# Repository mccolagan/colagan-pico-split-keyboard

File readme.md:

# ⌨️ Colagan V2 Right Only

> Clavier split custom - moitié droite uniquement avec layout AZERTY français

📖 **Page du projet :** https://mccolagan.github.io/colagan-pico-split-keyboard/ · 🛠️ Matériel (KiCad, PCB V2) : [`hardware/`](hardware/README.md)

> **Firmware actuel : split Vial des deux moitiés**, documenté dans [`firmware/README.md`](firmware/README.md)
> (compilation, flash, couches, couleurs par couche éditables depuis le configurateur web, protocole
> [`docs/led-stream-protocol.md`](docs/led-stream-protocol.md)). La suite de ce fichier décrit l'ancien
> firmware VIA « Right Only » et est conservée pour référence.

---

## ✨ Caractéristiques

- 🧠 **Processeur:** RP2040 (Raspberry Pi Pico)
- ⌨️ **Layout:** 30 touches (matrice 6×5)
- 🔌 **Configuration:** VIA (reconfiguration en temps réel)
- 💡 **RGB:** 30 LEDs SK6812 MINI-E (1 par touche) avec animations personnalisées
- 🖐️ **Ergonomie:** Ligne 5 en forme de "montagne" pour les pouces
- 🇫🇷 **Optimisé:** AZERTY français

---

## 🎮 Layers disponibles

Le clavier dispose de **6 layers**. Il est pensé pour jouer de la main droite (souris à gauche) : les couches de jeu envoient les **touches par défaut du jeu**, placées sous les doigts, pour ne jamais avoir à rebinder.

| Layer | Rôle | Accès |
|-------|------|-------|
| **BASE** | Côté droit de l'AZERTY | Défaut |
| **FN** | Côté gauche de l'AZERTY | Double-tap sur Ctrl |
| **FPS** | Warzone | Sélecteur |
| **MMO** | WoW | Sélecteur |
| **MMO_UI** | F1-F5 et fenêtres du jeu | Tenir la touche `UI` depuis MMO |
| **SEL** | Sélecteur de couche | Triple-tap sur Ctrl, ou tenir le pouce de droite en jeu |

### 🔀 Changer de layer

La touche de pouce tout à droite (matrice 4,4) fait office de Ctrl multi-tap sur BASE et FN (fenêtre de 500 ms entre deux taps) :

| Taps | Effet |
|------|-------|
| **1x** | Ctrl normal |
| **2x** | Toggle FN |
| **3x** | Ouvre/ferme le sélecteur SEL |

Dans le sélecteur, la rangée du haut propose : **BASE** (blanc), **FPS** (rouge), **MMO** (bleu), **FN** (vert). Un appui choisit la couche. Depuis FPS ou MMO, on **tient** le pouce de droite (en vert), on appuie sur la couche voulue, puis on relâche.

### 🎯 Layer BASE - Côté DROIT AZERTY

```
┌─────┬─────┬─────┬─────┬─────┬─────┐
│  -  │  è  │  _  │  ç  │  à  │  )  │
├─────┼─────┼─────┼─────┼─────┼─────┤
│  Y  │  U  │  I  │  O  │  P  │  ^  │
├─────┼─────┼─────┼─────┼─────┼─────┤
│  H  │  J  │  K  │  L  │  M  │  ù  │
├─────┼─────┼─────┼─────┼─────┼─────┤
│  B  │  N  │  ,  │  ;  │  :  │  !  │
├─────┼─────┼─────┼─────┼─────┼─────┤
│ Del │Bksp │ Ent │ Alt │Ctrl │     │
│     │     │     │     │ 2xFN│     │
└─────┴─────┴─────┴─────┴─────┴─────┘
```

### 🔤 Layer FN - Côté GAUCHE AZERTY

Double-tap sur Ctrl pour activer/désactiver

```
┌─────┬─────┬─────┬─────┬─────┬─────┐
│  ²  │  &  │  é  │  "  │  '  │  (  │
├─────┼─────┼─────┼─────┼─────┼─────┤
│ Tab │  A  │  Z  │  E  │  R  │  T  │
├─────┼─────┼─────┼─────┼─────┼─────┤
│Caps │  Q  │  S  │  D  │  F  │  G  │
├─────┼─────┼─────┼─────┼─────┼─────┤
│Shift│  <  │  W  │  X  │  C  │  V  │
├─────┼─────┼─────┼─────┼─────┼─────┤
│ Del │Bksp │ Ent │ Alt │Ctrl │     │
└─────┴─────┴─────┴─────┴─────┴─────┘
```

### 🔫 Layer FPS - Warzone

Touches par défaut du jeu (AZERTY côté OS). Le cluster ZQSD est au même endroit que sur la couche MMO.

```
┌─────┬─────┬─────┬─────┬─────┬─────┐
│  1  │  2  │  3  │  4  │  5  │ Tab │
├─────┼─────┼─────┼─────┼─────┼─────┤
│  C  │Shift│  Z  │  E  │  F  │  G  │
├─────┼─────┼─────┼─────┼─────┼─────┤
│  X  │  Q  │  S  │  D  │  R  │  V  │
├─────┼─────┼─────┼─────┼─────┼─────┤
│  M  │  T  │  /  │Bksp │ Ent │ Esc │
├─────┼─────┼─────┼─────┼─────┼─────┘
│ Spc │Ctrl │ Alt │     │ SEL │
└─────┴─────┴─────┴─────┴─────┘
```

### ⚔️ Layer MMO - WoW

`S1` à `S11` sont des emplacements de sorts, à lier dans le jeu (ou à remapper dans VIA). Shift, Ctrl et Alt aux pouces multiplient chaque emplacement.

```
┌─────┬─────┬─────┬─────┬─────┬─────┐
│ S1  │ S2  │ S3  │ S4  │ S5  │ S6  │
├─────┼─────┼─────┼─────┼─────┼─────┤
│ Tab │  A  │  Z  │  E  │ S7  │ S8  │
├─────┼─────┼─────┼─────┼─────┼─────┤
│NumLk│  Q  │  S  │  D  │ S9  │ S10 │
├─────┼─────┼─────┼─────┼─────┼─────┤
│ S11 │ UI  │  /  │Bksp │ Ent │ Esc │
├─────┼─────┼─────┼─────┼─────┼─────┘
│ Spc │Shift│Ctrl │ Alt │ SEL │
└─────┴─────┴─────┴─────┴─────┘
```

`S1` à `S10` envoient `1` à `0` (AZERTY : `& é " ' ( - è _ ç à`), `S11` envoie `-`. Tenir `UI` ouvre la sous-couche **MMO_UI** :

```
┌─────┬─────┬─────┬─────┬─────┬─────┐
│ F1  │ F2  │ F3  │ F4  │ F5  │  P  │
├─────┼─────┼─────┼─────┼─────┼─────┤
│     │     │     │     │  C  │  B  │
├─────┼─────┼─────┼─────┼─────┼─────┤
│     │     │     │     │  M  │  N  │
├─────┼─────┼─────┼─────┼─────┼─────┤
│  L  │     │     │     │     │     │
└─────┴─────┴─────┴─────┴─────┴─────┘
```

Les cases vides gardent la touche de la couche MMO.

### 🎛️ Layer SEL - Sélecteur

```
┌─────┬─────┬─────┬─────┬─────┬─────┐
│BASE │ FPS │ MMO │ FN  │     │     │
├─────┼─────┼─────┼─────┼─────┼─────┤
│ Br- │ Br+ │     │     │     │     │
└─────┴─────┴─────┴─────┴─────┴─────┘
```

**Couleurs RGB des couches de jeu :**
- 🔵 **BLEU** : armes 1-5 (FPS), sorts (MMO)
- ⚪ **BLANC** : ZQSD + Espace
- 🟡 **JAUNE** : modificateurs, Tab
- 🔴 **ROUGE** : actions de jeu (FPS)
- 🟣 **VIOLET** : touches de menu (Échap, Entrée, Retour, `/`)
- 🟢 **VERT** : sélecteur de couche, `UI`
- ⚫ **ÉTEINT** : touches inutilisées

La luminosité se règle depuis le sélecteur (**Br-** / **Br+**).

---

## 🚀 Quick Start

### 1️⃣ Compiler le firmware

```bash
./build.sh
```

Ce script :
- Synchronise les fichiers du projet vers QMK
- Compile le firmware
- Copie le `.uf2` dans le projet

### 2️⃣ Flasher le Pico

**Entrer en mode bootloader :**

- 🔹 **Méthode 1 :** Maintenir `BOOT` + appuyer `RESET` + relâcher `BOOT`
- 🔹 **Méthode 2 :** Double-tap rapide sur `RESET`

**Flasher automatiquement :**

```bash
./flash.sh
```

**Ou manuellement :**

```bash
sudo cp firmware.uf2 /media/$USER/RPI-RP2*/
```

✅ Le clavier redémarre automatiquement !

### 3️⃣ Reset EEPROM (première utilisation)

Pour appliquer la configuration par défaut du firmware (luminosité 10%, etc.) :

**Bootmagic Reset :**
1. Débranchez le clavier
2. Maintenez la touche en haut à gauche (position 0,0 - la touche "-")
3. Rebranchez le clavier tout en maintenant la touche
4. L'EEPROM sera réinitialisée

---

## 📁 Structure des fichiers

```
colagan-pico-split-keyboard/
├── 🔨 build.sh                    # Script de compilation + synchronisation
├── ⚡ flash.sh                    # Script de flash automatique
├── 📦 firmware.uf2                # Firmware compilé
├── ⚙️ keyboard.json               # Configuration matérielle QMK
├── 📖 readme.md                   # Ce fichier
└── 🗂️ keymaps/
    └── via/                       # Keymap VIA
        ├── keymap.c               # Layout des touches + RGB custom
        └── config.h               # Configuration (6 layers, luminosité)
```

---

## 🔧 Configuration matérielle

### 📌 Pins GPIO

- **Colonnes (6) :** `GP20`, `GP22`, `GP12`, `GP11`, `GP10`, `GP9`
- **Lignes (5) :** `GP21`, `GP19`, `GP18`, `GP17`, `GP16`
- **RGB LEDs :** `GP13` (SK6812 MINI-E data)

### 💡 RGB Matrix

- **LEDs :** 30 SK6812 MINI-E (1 par touche)
- **Câblage :** Serpentin (ligne 0: L→R, ligne 1: R→L, etc.)
- **Luminosité par défaut :** 10% (26/255)
- **Luminosité max :** 200/255

### 🔌 USB VID/PID

- **Vendor ID :** `0xFEED`
- **Product ID :** `0x0004`
- **Nom :** Colagan V2 Right Only

---

## 🎨 RGB Matrix

### Modes RGB

> Firmware Vial split : couleurs et effet par couche se règlent dans le configurateur web, voir
> [`firmware/README.md`](firmware/README.md#modifier-les-led). Ce qui suit concerne l'ancien firmware.

Le clavier dispose de 2 modes RGB distincts :

1. **Layers BASE/FN** : Animations RGB Matrix standards (40+ effets)
2. **Layers FPS/MMO/SEL** : Couleurs fixes personnalisées par touche (voir schémas ci-dessus)

### Contrôles RGB via VIA

Dans VIA (onglet **Lighting** → **QMK RGB Matrix**) :

| Keycode   | Action                         |
|-----------|--------------------------------|
| `RM_TOGG` | 💡 On/Off des LEDs            |
| `RM_NEXT` | ➡️ Animation suivante         |
| `RM_PREV` | ⬅️ Animation précédente       |
| `RM_VALU` | ☀️ Augmenter la luminosité    |
| `RM_VALD` | 🌙 Diminuer la luminosité     |
| `RM_HUEU` | 🔴 Augmenter la teinte        |
| `RM_HUED` | 🔵 Diminuer la teinte         |
| `RM_SATU` | ⬆️ Augmenter la saturation    |
| `RM_SATD` | ⬇️ Diminuer la saturation     |
| `RM_SPDU` | ⚡ Vitesse d'animation +       |
| `RM_SPDD` | 🐌 Vitesse d'animation -       |

**Note :** Sur les layers FPS, MMO et SEL, seuls les contrôles de luminosité (Br-/Br+ du sélecteur) fonctionnent. Les autres effets sont désactivés pour maintenir les couleurs personnalisées.

---

## 🎹 Configuration VIA

### 🔄 Correspondances AZERTY ↔ QWERTY

> ⚠️ VIA affiche en **QWERTY US**, mais votre OS utilise **AZERTY français**

| 🇫🇷 Pour obtenir (AZERTY) | 🇺🇸 Sélectionner dans VIA |
|---------------------------|---------------------------|
| `'` (apostrophe)          | `4`                       |
| `é`                       | `2`                       |
| `è`                       | `7`                       |
| `à`                       | `0`                       |
| `ù`                       | `'` (quote)               |
| `ç`                       | `9`                       |
| `-` (tiret)               | `6`                       |
| `A`                       | `Q`                       |
| `Q`                       | `A`                       |
| `W`                       | `Z`                       |
| `Z`                       | `W`                       |
| `M`                       | `;`                       |
| `,` (virgule)             | `M`                       |

---

## 🛠️ Dépannage

### ❌ VIA ne détecte pas le clavier

1. ✅ Vérifiez que le firmware a été compilé avec `-km via`
2. 🔄 Rechargez la page VIA
3. 🔌 Vérifiez la connexion USB :
   ```bash
   lsusb | grep -i feed
   # Devrait afficher : ID feed:0004 Colagan V2 Right Only
   ```

### 🔤 Les touches ne correspondent pas

➡️ **Normal !** VIA affiche en QWERTY, votre OS est en AZERTY.
📋 Référez-vous au tableau de correspondances ci-dessus.

### 💡 Le clavier démarre avec des couleurs RGB étranges

C'est normal ! Le clavier démarre en layer BASE avec les animations RGB par défaut.

Pour utiliser les layers de jeu :
- Triple-tap sur Ctrl (touche en bas à droite), puis choisir FPS ou MMO

Pour désactiver le RGB au démarrage :
- Utilisez VIA pour assigner `RM_TOGG` à une touche et éteindre le RGB

### 🎮 Les layers de jeu ne démarrent pas avec la bonne luminosité

Si la luminosité est à 0 après un flash :

1. Débranchez le clavier
2. Maintenez la touche en haut à gauche ("-")
3. Rebranchez le clavier (Bootmagic Reset)
4. La luminosité sera réinitialisée à 10%

### 🔄 Reset de la configuration

**Bootmagic Reset (recommandé) :**
- Débranchez le clavier
- Maintenez la touche en haut à gauche (L0C0)
- Rebranchez le clavier

**Via VIA :**
- Settings ⚙️ → "Clear EEPROM"
- Déconnectez/reconnectez le clavier

---

## 📚 Commandes utiles

```bash
# 🔨 Compiler et synchroniser
./build.sh

# ⚡ Flasher
./flash.sh

# 🧹 Nettoyer les fichiers de compilation
cd ~/qmk_firmware
~/qmk_env/bin/qmk clean

# 🩺 Vérifier la configuration QMK
~/qmk_env/bin/qmk doctor

# ℹ️ Informations du clavier
~/qmk_env/bin/qmk info -kb colagan_v2_right_only
```

---

## 🔗 Ressources

- 🌐 [VIA Web App](https://usevia.app)
- 📖 [Documentation VIA](https://www.caniusevia.com/)
- 📚 [Documentation QMK](https://docs.qmk.fm/)
- 🔧 [QMK VIA Support](https://docs.qmk.fm/features/via)
- 🔌 [Configuration RP2040](https://docs.qmk.fm/platformdev_rp2040)

---

## 📄 License

GPL-2.0-or-later

---

## 🎯 Notes de développement

### Custom RGB Gaming Layers

Les layers FPS, MMO et SEL utilisent `rgb_matrix_indicators_user()` pour définir des couleurs personnalisées par touche :
- Les couleurs sont proportionnelles à la luminosité globale (`rgb_matrix_get_val()`)
- Les touches Br+/Br- (layer SEL) appellent directement `rgb_matrix_increase_val()` et `rgb_matrix_decrease_val()`
- Le mapping LED suit la chaîne linéaire du PCB : index = ligne × 6 + colonne (pouces : 24 à 28)

### Multi-tap Ctrl Key

La touche Ctrl (position 4,4) utilise un système de multi-tap :
- Délai de détection : `CTRL_MULTITAP_TERM` (500ms)
- 1 tap : Ctrl normal
- 2 taps : Toggle layer FN
- 3 taps : Ouvre/ferme le sélecteur SEL (`TO()` vers BASE, FPS, MMO ou FN)

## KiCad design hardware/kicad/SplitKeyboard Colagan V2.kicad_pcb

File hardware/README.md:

# Matériel — Colagan Pico Split KeyBoard V2

Sources KiCad (9.0) du PCB réversible tel que fabriqué chez JLCPCB (novembre 2025) : 29 touches Gateron KS-33 low profile en hot-swap, une LED SK6812 mini-e et une diode par touche, Raspberry Pi Pico (W), USB-C 16 broches. Le même circuit sert pour les deux moitiés, en le retournant.

## Ouvrir le projet

Ouvrir `kicad/SplitKeyboard Colagan V2.kicad_pro` avec KiCad 9. Le fichier `fp-lib-table` déclare la bibliothèque d'empreintes du projet (`Library SplitKeyboard Colagan`), donc rien à configurer. Les symboles sont embarqués dans le schéma ; les bibliothèques standard de KiCad (`Connector`, `MCU_Module_RaspberryPi_Pico`, `power`, `MountingHole`) viennent de l'installation.

| Fichier | Contenu |
|---|---|
| `kicad/SplitKeyboard Colagan V2.kicad_{pro,sch,pcb}` | Projet principal (version fabriquée, 04/11/2025) |
| `kicad/Library SplitKeyboard Colagan.pretty/` | Toutes les empreintes personnalisées (voir ci-dessous) |
| `kicad/fp-lib-table` | Table de bibliothèques du projet |
| `kicad/fabrication-toolkit-options.json` | Options du plugin de fabrication |
| `images/` | Rendus 3D (face, dos), cuivre avant/arrière et schéma en SVG, générés avec `kicad-cli` |
| `3d/` | Export STEP et 3MF de la V1 (ancienne révision) |

Les anciennes sources (révision du 20/10/2025, variante OLED, captures) ne sont plus dans le dépôt : elles sont dans l'historique git.

## Empreintes (`Library SplitKeyboard Colagan.pretty`)

### Utilisées dans le PCB

| Empreinte | Rôle | Quantité |
|---|---|---|
| `KS33-HS-Colagan-1U-Final` | Touche 1U : interrupteur KS33 hot-swap, LED SK6812 mini-e, diode ; réversible (deux faces) | 25 |
| `KS33-HS-Colagan-1.5U-Final` | Même chose pour la colonne extérieure 1,5U | 4 |
| `RaspberryPi_Pico_Colagan_REF3` | Support du Raspberry Pi Pico | 1 |
| `USB_C_16P-Reversible-colagan` | Connecteur USB-C 16 broches (alimentation et lien série entre les moitiés) | 1 |
| `Capasitor_SMD_1206_Reversible_ColaganV3` | Résistances 5,1 kΩ de CC1/CC2 (R1, R2), réversibles | 2 |
| `qrcode github` | QR code du projet, en sérigraphie/cuivre | 1 |

La touche KS33 intègre trois composants en un seul placement : c'est une empreinte combinée, pas une empreinte d'interrupteur seule. Broches : 1 colonne, 2 et 3 ligne (via la diode), 4 +5V, 5 DIN de la LED, 6 GND, 7 DOUT de la LED.

### Versions intermédiaires et illustrations

- `Capasitor_*` autres que V3, `SOT-23-5-Reversible-*`, `USB_C_6P_Colagan`, `OLED_SSD1306_128x32_4pin`, `RaspberryPi_Pico_Colagan`, `_REF`, `_REF2` : itérations précédentes, non utilisées dans la V2.
- `Gengar*`, `Gengar_Souls.kicad_sym`, `fantominus*`, `spectrum 35mm` : illustrations de sérigraphie / cuivre (empreintes « LOGO »).

## Modèles 3D

Les empreintes référencent des modèles 3D qui **ne sont pas dans ce dépôt** :

- le modèle Gateron KS-33 low profile (`GateronKS-33LowProfile-3D/*.stp`, fourni par le fabricant) ;
- le modèle du switch de la bibliothèque `marbastlib` d'ebastler (installée via le gestionnaire de plugins de KiCad) ;
- un modèle `SK6812-E.step` stocké localement ;
- les modèles du Pico de la bibliothèque standard de KiCad.

Les empreintes fonctionnent sans eux ; seul l'affichage 3D dans KiCad en dépend. Le dossier `3d/` contient un export complet de la carte.

## Électronique

- **Matrice** : colonnes `Col0`–`Col5`, rangées `Row0`–`Row4`, diodes sur les touches. Brochage du Pico : colonnes GP20, GP22, GP12, GP11, GP10, GP9 ; rangées GP21, GP19, GP18, GP17, GP16 ; LEDs GP13.
- **LEDs** : chaîne linéaire, LED n = touche CH(n+1) (CH1 à CH29, de gauche à droite sur chaque rangée). Alimentées en 5 V.
- **Signal LED** : la ligne de données du Pico (3,3 V) attaque directement la première LED, sans convertisseur de niveau ni résistance (validé sur les deux moitiés, LED alimentées en 5 V). Les sources V2 n'ont pas de U3 ni de 4k7.
- **USB-C** : prise `J2` 16 broches (V2), avec deux résistances de 5,1 kΩ (R1, R2) sur CC1/CC2. Les broches de données D+/D- (A6/B6, A7/B7) sont reliées directement aux signaux `SCL` et `SDA` : c'est le lien série entre les deux moitiés.
- **Géométrie** : grille 6×4 au pas de 19,05 mm ; colonne extérieure 1,5U ; cinq pouces CH25–CH29 en arc (rotations 45°, 22,5°, 0°, −22,5°, −45° dans KiCad).

Brochage de la moitié gauche (carte retournée) : voir la section de montage ci-dessous. Détails lus sur le PCB V2 et validés sur les deux moitiés en octobre 2026.

## Non inclus

Les exports STEP lourds, les modèles 3D du switch, les Gerbers de fabrication et les sauvegardes automatiques de KiCad.

## Licence

Aucune licence matérielle n'est encore déclarée pour ces fichiers.

## Montage de la moitié gauche (retournée)

Le PCB est réversible : la gauche est la même carte retournée, avec le Pico dans le même sens. Conséquences vérifiées en octobre 2026 :
- Les étiquettes `NO PIN` et `+5V` sont inversées côté gauche. Les deux trous sont sur le rail 5 V : souder VBUS (broche 40 du Pico) dans l'un, ne jamais souder GP0 (broche 1) dans l'autre, sous peine d'injecter 5 V dans un GPIO.
- Le brochage est le miroir de la droite : LED sur GP18 (GP13 à droite), matrice colonnes GP11, GP9, GP19, GP20, GP21, GP22 et lignes GP10, GP12, GP13, GP14, GP15, lien série sur GP26.
- SK6812 mini-E : la broche marquée de la LED est le GND, pas le VDD. Souder à la pâte a donné des contacts intermittents, mieux vaut un fer.
- Diodes : cathode côté ligne (`COL2ROW`), le sens visuel est inversé d'une face à l'autre.

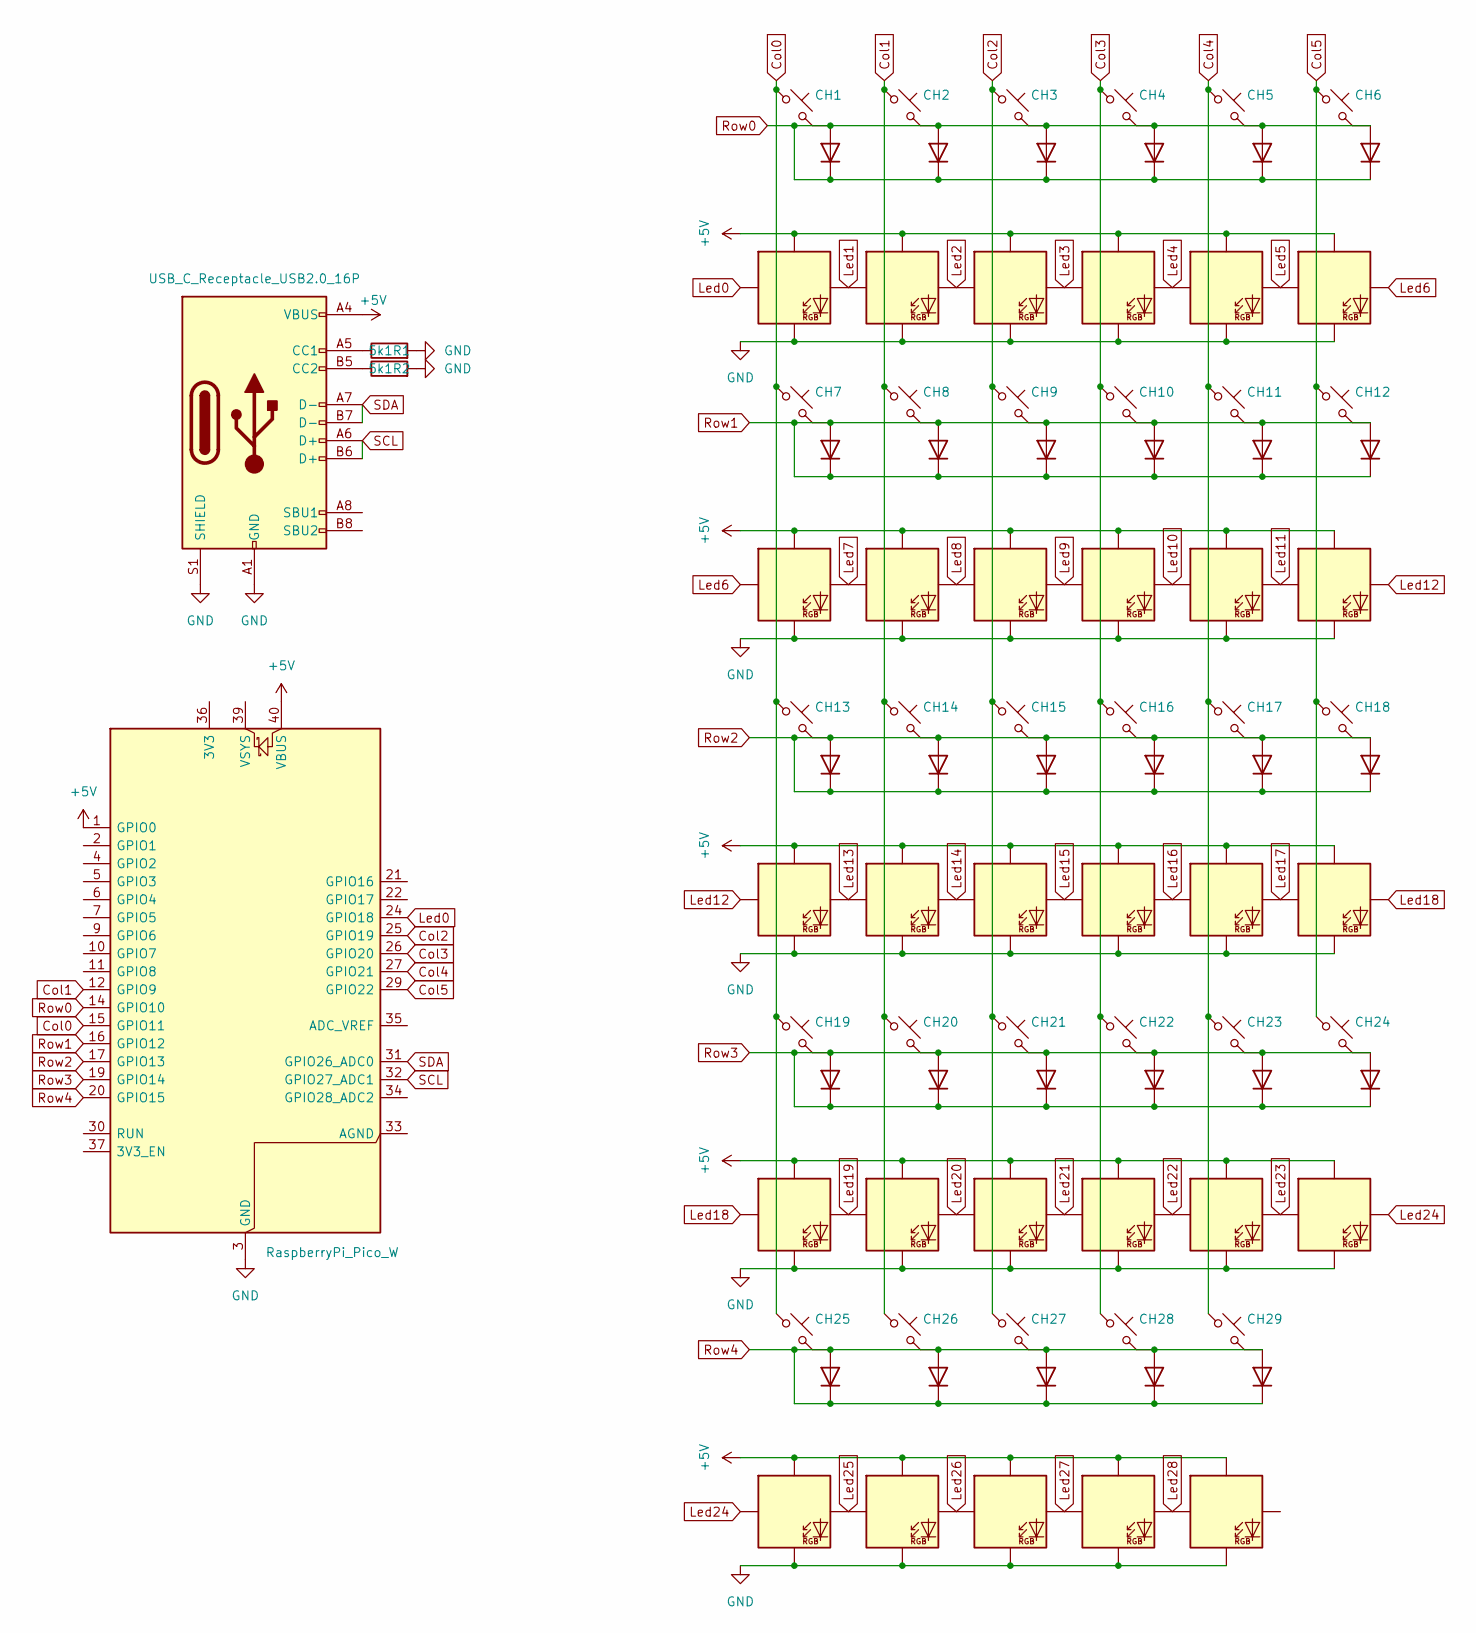
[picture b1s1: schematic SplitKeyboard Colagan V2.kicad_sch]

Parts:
5k1R1: R1; Capasitor_SMD_1206_Reversible_ColaganV3
5k1R2: Capasitor_SMD_1206_Reversible_ColaganV3
A1: RaspberryPi_Pico_W; RaspberryPi_Pico_Colagan_REF3
CH1, CH2, CH3, CH4, CH5, CH7, CH8, CH9, CH10, CH11, CH13, CH14, CH15, CH16, CH17, CH19, CH20, CH21, CH22, CH23, CH25, CH26, CH27, CH28, CH29: KS33_SW_HS; KS33-HS-Colagan-1U-Final
CH6, CH12, CH18, CH24: KS33_SW_HS; KS33-HS-Colagan-1.5U-Final
J2: USB_C_Receptacle_USB2.0_16P; USB_C_16P-Reversible-colagan

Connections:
+5V: A1.1 (GPIO0), A1.40 (VBUS), CH1.4 (VDD), CH2.4 (VDD), CH3.4 (VDD), CH4.4 (VDD), CH5.4 (VDD), CH6.4 (VDD), CH7.4 (VDD), CH8.4 (VDD), CH9.4 (VDD), CH10.4 (VDD), CH11.4 (VDD), CH12.4 (VDD), CH13.4 (VDD), CH14.4 (VDD), CH15.4 (VDD), CH16.4 (VDD), CH17.4 (VDD), CH18.4 (VDD), CH19.4 (VDD), CH20.4 (VDD), CH21.4 (VDD), CH22.4 (VDD), CH23.4 (VDD), CH24.4 (VDD), CH25.4 (VDD), CH26.4 (VDD), CH27.4 (VDD), CH28.4 (VDD), CH29.4 (VDD), J2.A4 (VBUS), J2.A9 (VBUS), J2.B4 (VBUS), J2.B9 (VBUS)
Col0: A1.15 (GPIO11), CH1.1, CH7.1, CH13.1, CH19.1, CH25.1
Col1: A1.12 (GPIO9), CH2.1, CH8.1, CH14.1, CH20.1, CH26.1
Col2: A1.25 (GPIO19), CH3.1, CH9.1, CH15.1, CH21.1, CH27.1
Col3: A1.26 (GPIO20), CH4.1, CH10.1, CH16.1, CH22.1, CH28.1
Col4: A1.27 (GPIO21), CH5.1, CH11.1, CH17.1, CH23.1, CH29.1
Col5: A1.29 (GPIO22), CH6.1, CH12.1, CH18.1, CH24.1
GND: 5k1R1.2, 5k1R2.2, A1.3 (GND), A1.8 (GND), A1.13 (GND), A1.18 (GND), A1.23 (GND), A1.28 (GND), A1.38 (GND), CH1.6 (VSS), CH2.6 (VSS), CH3.6 (VSS), CH4.6 (VSS), CH5.6 (VSS), CH6.6 (VSS), CH7.6 (VSS), CH8.6 (VSS), CH9.6 (VSS), CH10.6 (VSS), CH11.6 (VSS), CH12.6 (VSS), CH13.6 (VSS), CH14.6 (VSS), CH15.6 (VSS), CH16.6 (VSS), CH17.6 (VSS), CH18.6 (VSS), CH19.6 (VSS), CH20.6 (VSS), CH21.6 (VSS), CH22.6 (VSS), CH23.6 (VSS), CH24.6 (VSS), CH25.6 (VSS), CH26.6 (VSS), CH27.6 (VSS), CH28.6 (VSS), CH29.6 (VSS), J2.A1 (GND), J2.A12 (GND), J2.B1 (GND), J2.B12 (GND), J2.S1 (SHIELD)
Led0: A1.24 (GPIO18), CH1.5 (DIN)
Led1: CH1.7 (DOUT), CH2.5 (DIN)
Led2: CH2.7 (DOUT), CH3.5 (DIN)
Led3: CH3.7 (DOUT), CH4.5 (DIN)
Led4: CH4.7 (DOUT), CH5.5 (DIN)
Led5: CH5.7 (DOUT), CH6.5 (DIN)
Led6: CH6.7 (DOUT), CH7.5 (DIN)
Led7: CH7.7 (DOUT), CH8.5 (DIN)
Led8: CH8.7 (DOUT), CH9.5 (DIN)
Led9: CH9.7 (DOUT), CH10.5 (DIN)
Led10: CH10.7 (DOUT), CH11.5 (DIN)
Led11: CH11.7 (DOUT), CH12.5 (DIN)
Led12: CH12.7 (DOUT), CH13.5 (DIN)
Led13: CH13.7 (DOUT), CH14.5 (DIN)
Led14: CH14.7 (DOUT), CH15.5 (DIN)
Led15: CH15.7 (DOUT), CH16.5 (DIN)
Led16: CH16.7 (DOUT), CH17.5 (DIN)
Led17: CH17.7 (DOUT), CH18.5 (DIN)
Led18: CH18.7 (DOUT), CH19.5 (DIN)
Led19: CH19.7 (DOUT), CH20.5 (DIN)
Led20: CH20.7 (DOUT), CH21.5 (DIN)
Led21: CH21.7 (DOUT), CH22.5 (DIN)
Led22: CH22.7 (DOUT), CH23.5 (DIN)
Led23: CH23.7 (DOUT), CH24.5 (DIN)
Led24: CH24.7 (DOUT), CH25.5 (DIN)
Led25: CH25.7 (DOUT), CH26.5 (DIN)
Led26: CH26.7 (DOUT), CH27.5 (DIN)
Led27: CH27.7 (DOUT), CH28.5 (DIN)
Led28: CH28.7 (DOUT), CH29.5 (DIN)
unnamed: 5k1R1.1, J2.A5 (CC1)
unnamed: 5k1R2.1, J2.B5 (CC2)
Row0: A1.14 (GPIO10), CH1.2, CH1.3, CH2.2, CH2.3, CH3.2, CH3.3, CH4.2, CH4.3, CH5.2, CH5.3, CH6.2, CH6.3
Row1: A1.16 (GPIO12), CH7.2, CH7.3, CH8.2, CH8.3, CH9.2, CH9.3, CH10.2, CH10.3, CH11.2, CH11.3, CH12.2, CH12.3
Row2: A1.17 (GPIO13), CH13.2, CH13.3, CH14.2, CH14.3, CH15.2, CH15.3, CH16.2, CH16.3, CH17.2, CH17.3, CH18.2, CH18.3
Row3: A1.19 (GPIO14), CH19.2, CH19.3, CH20.2, CH20.3, CH21.2, CH21.3, CH22.2, CH22.3, CH23.2, CH23.3, CH24.2, CH24.3
Row4: A1.20 (GPIO15), CH25.2, CH25.3, CH26.2, CH26.3, CH27.2, CH27.3, CH28.2, CH28.3, CH29.2, CH29.3
SCL: A1.32 (GPIO27_ADC1), J2.A6 (D+), J2.B6 (D+)
SDA: A1.31 (GPIO26_ADC0), J2.A7 (D-), J2.B7 (D-)

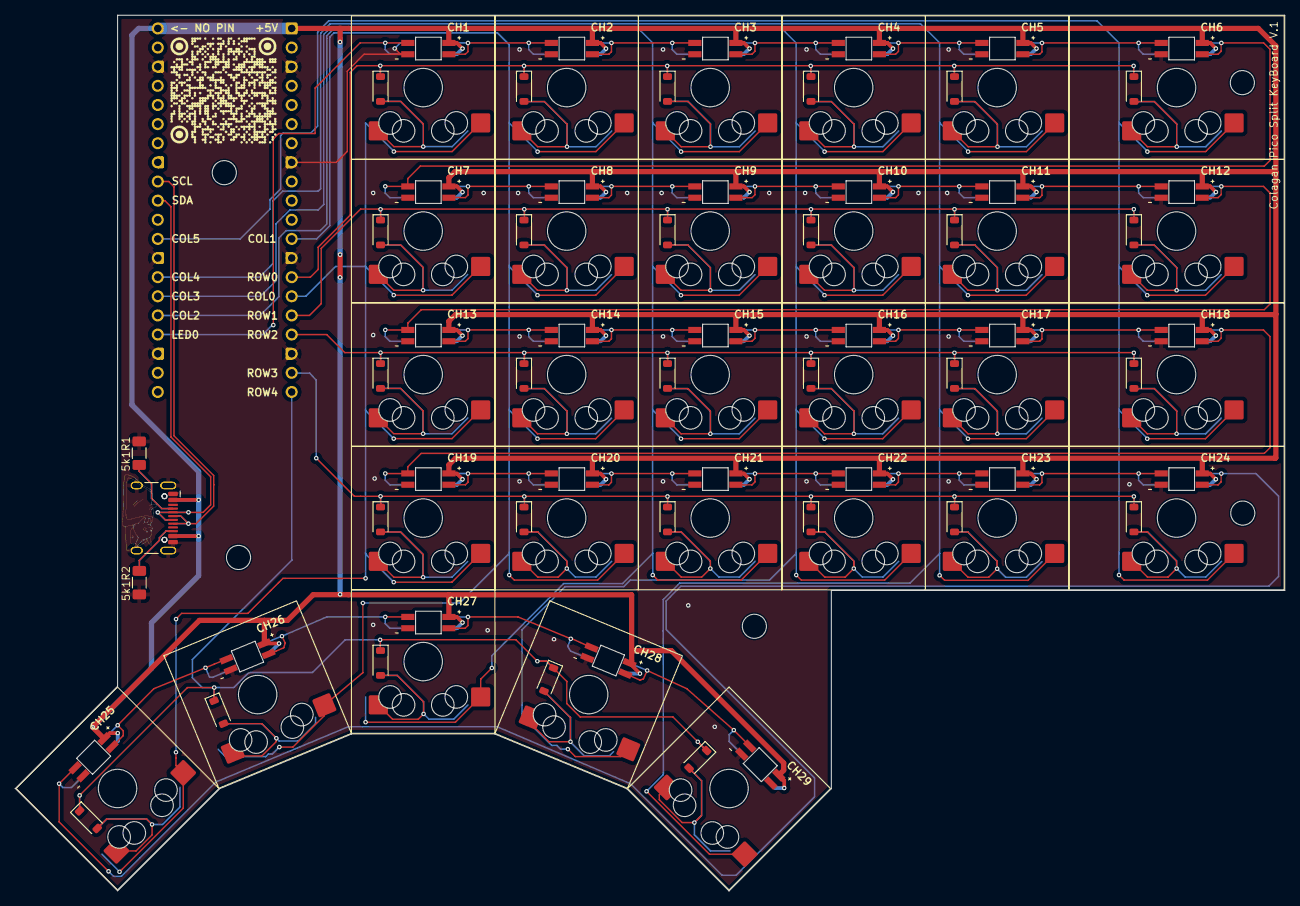
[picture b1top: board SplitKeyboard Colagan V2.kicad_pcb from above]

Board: 2 copper layers, 168.5 x 116.3 mm, 33 parts (1 on the bottom side), 46 nets.

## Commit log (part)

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2025-11-22 V0.1
2025-11-23 v0.2
2025-11-23 v0.2 test rgb
2025-11-23 v0.2 rgb ok
2025-11-23 v0.2 clean
2025-11-23 v0.3 gaming layout
